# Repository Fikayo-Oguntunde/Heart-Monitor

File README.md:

# Heart-Monitor
Monitor for heart beat.

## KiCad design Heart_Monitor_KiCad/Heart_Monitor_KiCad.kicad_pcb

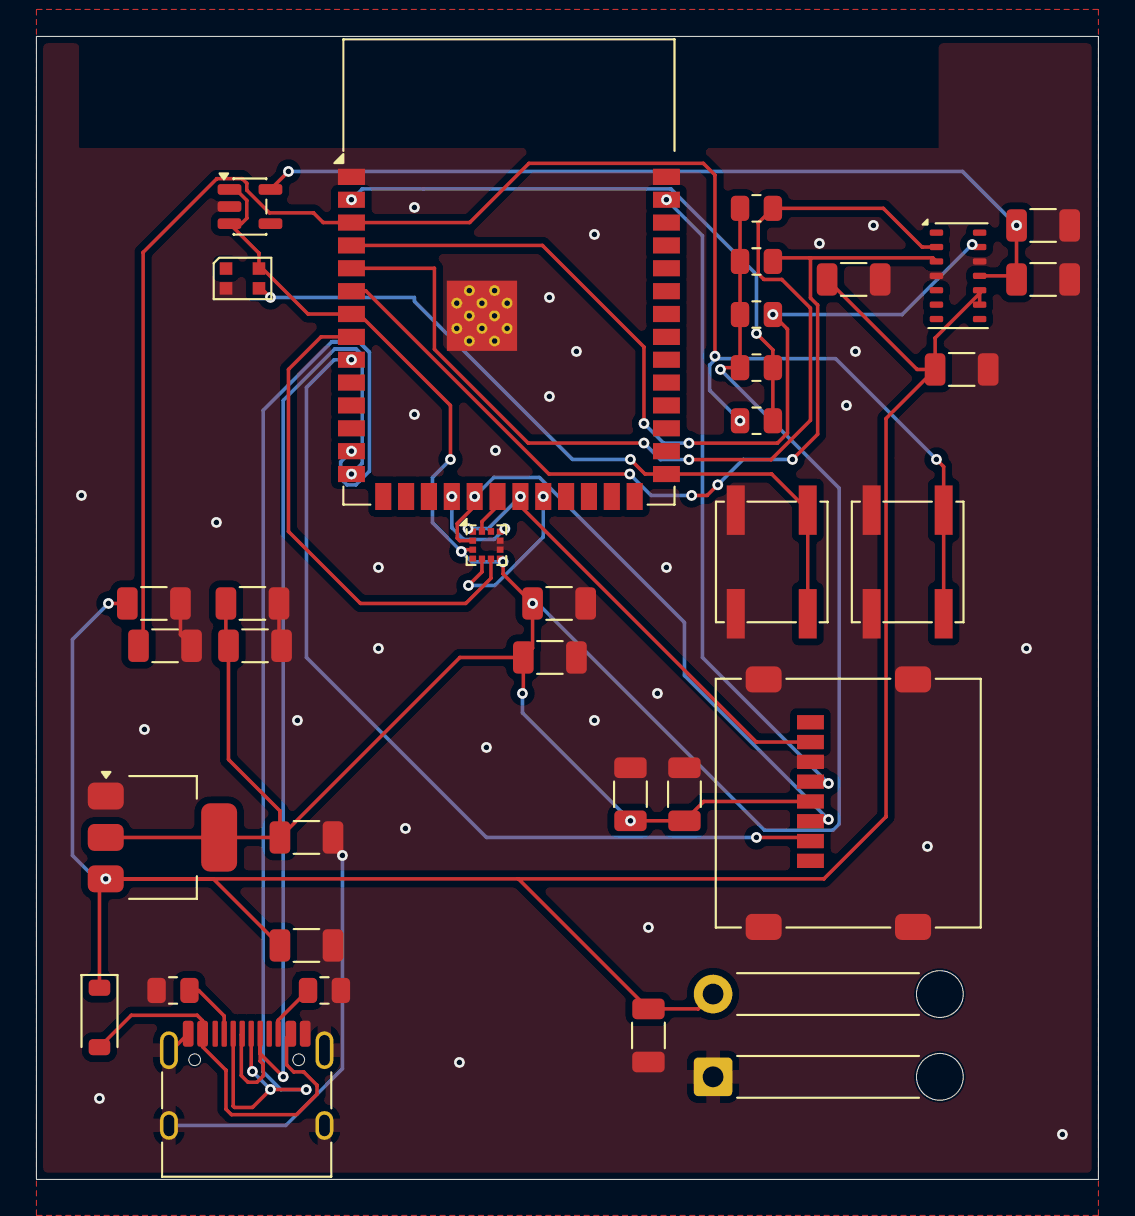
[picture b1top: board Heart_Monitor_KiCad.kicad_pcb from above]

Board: 2 copper layers, 59.0 x 63.5 mm, 34 parts (0 on the bottom side), 23 nets.

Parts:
C1: 4.7uF; C_1206_3216Metric
C2, C4, C12, C15: 0.1uF; C_1206_3216Metric
C3, C5, C6, C9, C13, C16, C17: 10uF; C_1206_3216Metric
C10, C11: 100nF; C_1206_3216Metric
C14: 1uF; C_1206_3216Metric
D1: 1N5817; D_SOD-123
D6: WS2812B-2020; LED_WS2812B-2020_PLCC4_2.0x2.0mm
J2: Conn_01x02; SolderWire-0.5sqmm_1x02_P4.6mm_D0.9mm_OD2.1mm_Relief
J3: USB_C_Receptacle_USB2.0_16P; USB_C_Receptacle_HRO_TYPE-C-31-M-12
J4: Micro_SD_Card; microSD_HC_Molex_47219-2001
R1, R2, R3: 4.7k; R_0805_2012Metric
R4, R5: 5.1k; R_0805_2012Metric
R11: 0; R_0805_2012Metric
R12: 10K; R_0805_2012Metric
SW2, SW3: SW_Push; SW_SPST_EVQP0
U1: MAX30102; Maxim_OLGA-14_3.3x5.6mm_P0.8mm
U2: ESP32-S3-WROOM-1
U3: AMS1117-3.3; SOT-223-3_TabPin2
U4: BMA400; LGA-12_2x2mm_P0.5mm
U6: MIC5504-1.8YM5; SOT-23-5

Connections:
+1V8: C1.1, C2.1, U1.11 (VDD), U6.5 (VOUT)
+5V: C3.1, C4.1, C5.1, C6.1, C17.1, D1.1 (K), J2.2, U1.9 (VLED+), U1.10 (VLED+), U3.3 (VI)
/CHIP_PU: C14.1, R12.1, SW3.2, U2.3 (EN)
/CLK: J4.5 (CLK), U2.39 (IO1)
/CSB_BMA400: U2.18 (IO10), U4.10 (CSB)
/ESP_3V3: R11.2, R12.2, U2.2 (3V3)
/GPIO0: D6.3 (DIN), SW2.2, U2.27 (IO0)
/GPIO19: J3.A7 (D-), J3.B7 (D-), U2.13 (USB_D-)
/GPIO20: J3.A6 (D+), J3.B6 (D+), U2.14 (USB_D+)
/INT1_BMA400: U2.22 (IO14), U4.5 (INT1)
/INT2_BMA400: U2.8 (IO15), U4.6 (INT2)
/INT_MAX30101_conn: R3.2, U1.13 (~INT), U2.4 (IO4)
/MISO: J4.7 (DAT0), U2.21 (IO13), U4.1 (SDO)
/MOSI: J4.3 (CMD), U2.19 (IO11), U4.2 (SDX)
/SCK: U2.20 (IO12), U4.12 (SCX)
/SCL_MAX30101_conn: R1.2, U1.2 (SCL), U2.5 (IO5)
/SDA_MAX30101_conn: R2.2, U1.3 (SDA), U2.6 (IO6)
/SD_DAT3_CD: J4.2 (DAT3/CD), U2.9 (IO16)
/SD_VDD: C9.1, C10.1, C11.1, C12.1, C13.1, C15.1, C16.1, D6.4 (VDD), J4.4 (VDD), R1.1, R2.1, R3.1, R11.1, U2.7 (IO7), U3.2 (VO), U4.3 (VDDIO), U4.7 (VDD), U6.1 (VIN), U6.3 (EN)
/VBUS: D1.2 (A), J3.A4 (VBUS), J3.A9 (VBUS), J3.B4 (VBUS), J3.B9 (VBUS)
GND: C1.2, C2.2, C3.2, C4.2, C5.2, C6.2, C9.2, C10.2, C11.2, C12.2, C13.2, C14.2, C15.2, C16.2, C17.2, D6.2 (VSS), J2.1, J3.A1 (GND), J3.A12 (GND), J3.B1 (GND), J3.B12 (GND), J3.SH (SHIELD), J4.6 (VSS), J4.SH (SHIELD), R4.1, R5.1, SW2.1, SW3.1, U1.4 (PGND), U1.12 (GND), U2.1 (GND), U2.40 (GND), U2.41 (GND), U3.1 (GND), U4.8 (GNDIO), U4.9 (GND), U6.2 (GND)
unnamed: J3.A5 (CC1), R4.2
unnamed: J3.B5 (CC2), R5.2
